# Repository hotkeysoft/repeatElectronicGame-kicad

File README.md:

# Wizard Electronic Game
Rev A October 2019

### Handheld Electronic Game
- ATmega328P microcontroller running at 12MHz
- 4 LEDs
- 4 buttons for play / mode selection
- Buzzer
- Tag-Connect for programming
- Runs on 3 AAA batteries

The microcontroller runs a [TMS1000-series emulator](https://github.com/hotkeysoft/emulators) I made (running in TMS1700 mode).

One ROM is loaded on the emulator: **Pocket Repeat** (by *Tandy/Radio-Shack*).  This is a Simon game clone.

Images
============
|Front                                                 | Back                                              |
|------------------------------------------------------|---------------------------------------------------|
|||

### Schematics (pdf)
- [Complete schematics](./img/schema.pdf)

### PCB Images (svg)
- [Top](./img/pcb-front.svg)
- [Bottom](./img/pcb-back.svg)

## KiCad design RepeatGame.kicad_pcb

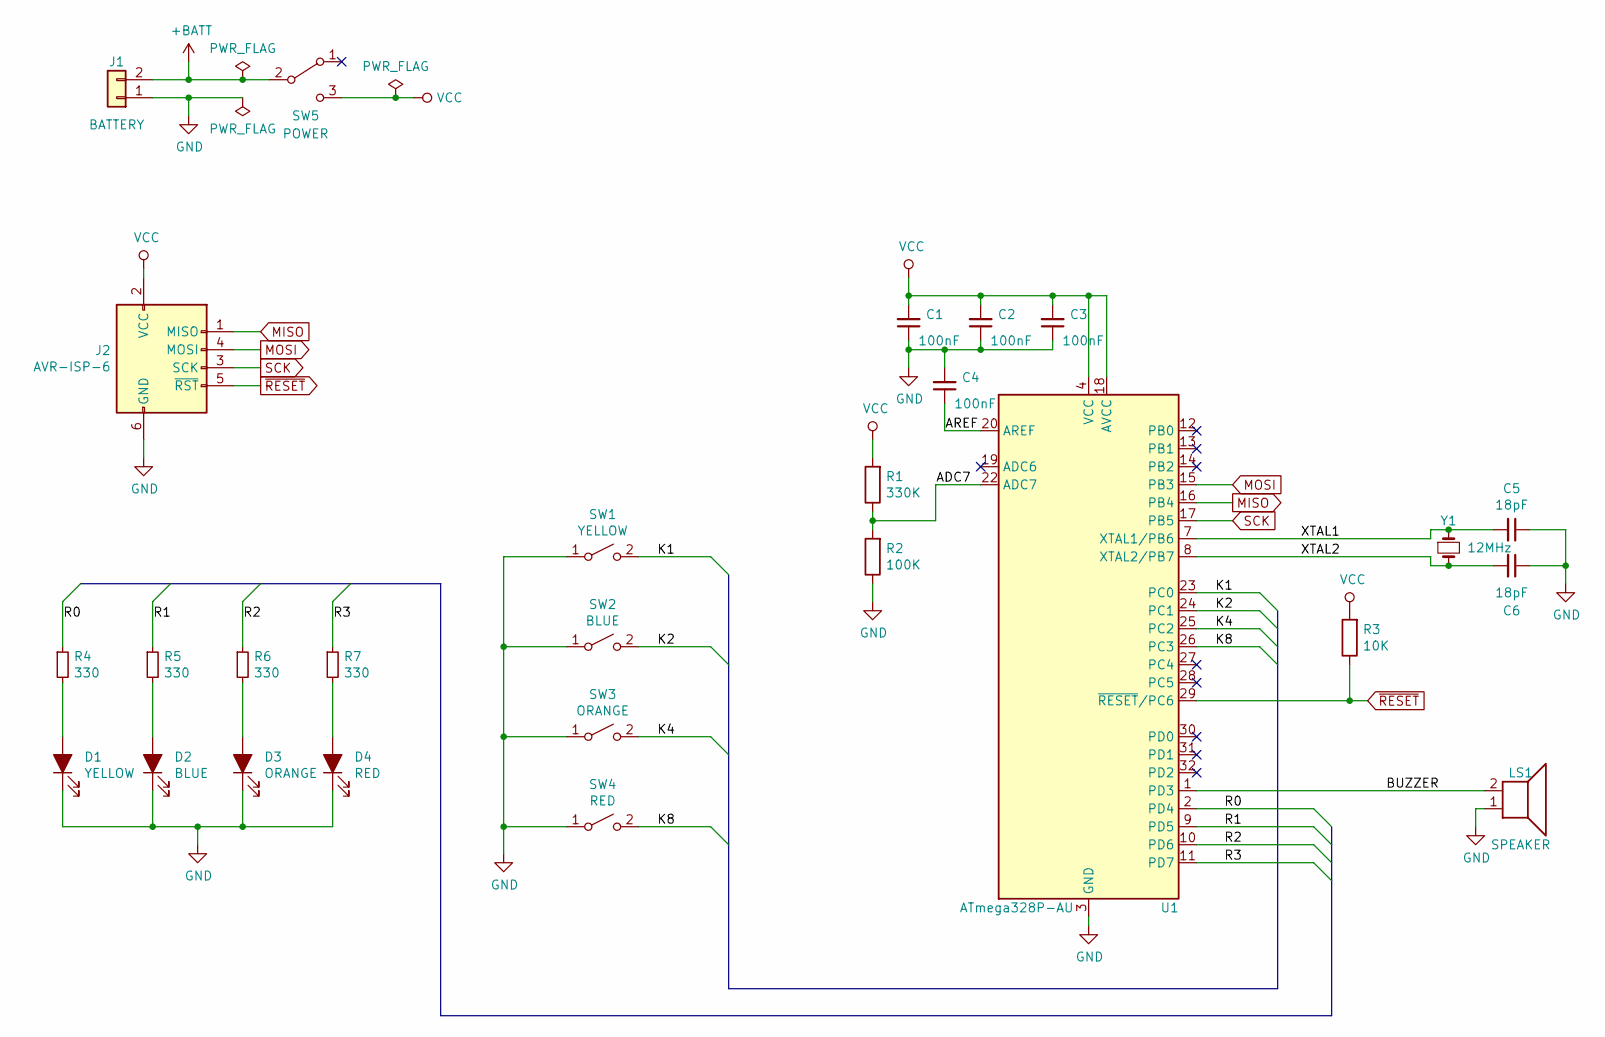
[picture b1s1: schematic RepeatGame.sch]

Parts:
C1, C2, C3, C4: 100nF; C_0805_2012Metric_Pad1.15x1.40mm_HandSolder
C5, C6: 18pF; C_0805_2012Metric_Pad1.15x1.40mm_HandSolder
D1: YELLOW; LED_1206_3216Metric
D2: BLUE; LED_1206_3216Metric
D3: ORANGE; LED_1206_3216Metric
D4: RED; LED_1206_3216Metric
J1: BATTERY; PinHeader_1x02_P2.54mm_Vertical
J2: AVR-ISP-6; Tag-Connect_TC2030-IDC-NL_2x03_P1.27mm_Vertical
LS1: SPEAKER; PinHeader_1x02_P2.54mm_Vertical
R1: 330K; R_0805_2012Metric_Pad1.15x1.40mm_HandSolder
R2: 100K; R_0805_2012Metric_Pad1.15x1.40mm_HandSolder
R3: 10K; R_0805_2012Metric_Pad1.15x1.40mm_HandSolder
R4, R5, R6, R7: 330; R_0805_2012Metric_Pad1.15x1.40mm_HandSolder
SW1: YELLOW; SW_PUSH_6mm
SW2: BLUE; SW_PUSH_6mm
SW3: ORANGE; SW_PUSH_6mm
SW4: RED; SW_PUSH_6mm
SW5: POWER; SW_CuK_OS102011MA1QN1_SPDT_Angled
U1: ATmega328P-AU; TQFP-32_7x7mm_P0.8mm
Y1: 12MHz; Crystal_HC49-4H_Vertical

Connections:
+BATT: J1.2, SW5.2 (B)
/ADC7: R1.1, R2.2, U1.22 (ADC7)
/AREF: C4.1, U1.20 (AREF)
/BUZZER: LS1.2, U1.1 (PD3)
/K1: SW1.2 (B), U1.23 (PC0)
/K2: SW2.2 (B), U1.24 (PC1)
/K4: SW3.2 (B), U1.25 (PC2)
/K8: SW4.2 (B), U1.26 (PC3)
/R0: R4.1, U1.2 (PD4)
/R1: R5.1, U1.9 (PD5)
/R2: R6.1, U1.10 (PD6)
/R3: R7.1, U1.11 (PD7)
/XTAL1: C5.2, U1.7 (XTAL1/PB6), Y1.1
/XTAL2: C6.2, U1.8 (XTAL2/PB7), Y1.2
GND: C1.1, C2.1, C3.1, C4.2, C5.1, C6.1, D1.1 (K), D2.1 (K), D3.1 (K), D4.1 (K), J1.1, J2.6 (GND), LS1.1, R2.1, SW1.1 (A), SW2.1 (A), SW3.1 (A), SW4.1 (A), U1.3 (GND), U1.5 (GND), U1.21 (GND)
MISO: J2.1 (MISO), U1.16 (PB4)
MOSI: J2.4 (MOSI), U1.15 (PB3)
unnamed: D1.2 (A), R4.2
unnamed: D2.2 (A), R5.2
unnamed: D3.2 (A), R6.2
unnamed: D4.2 (A), R7.2
SCK: J2.3 (SCK), U1.17 (PB5)
VCC: C1.2, C2.2, C3.2, J2.2 (VCC), R1.2, R3.2, SW5.3 (C), U1.4 (VCC), U1.6 (VCC), U1.18 (AVCC)
~RESET: J2.5 (~RST), R3.1, U1.29 (~RESET~/PC6)

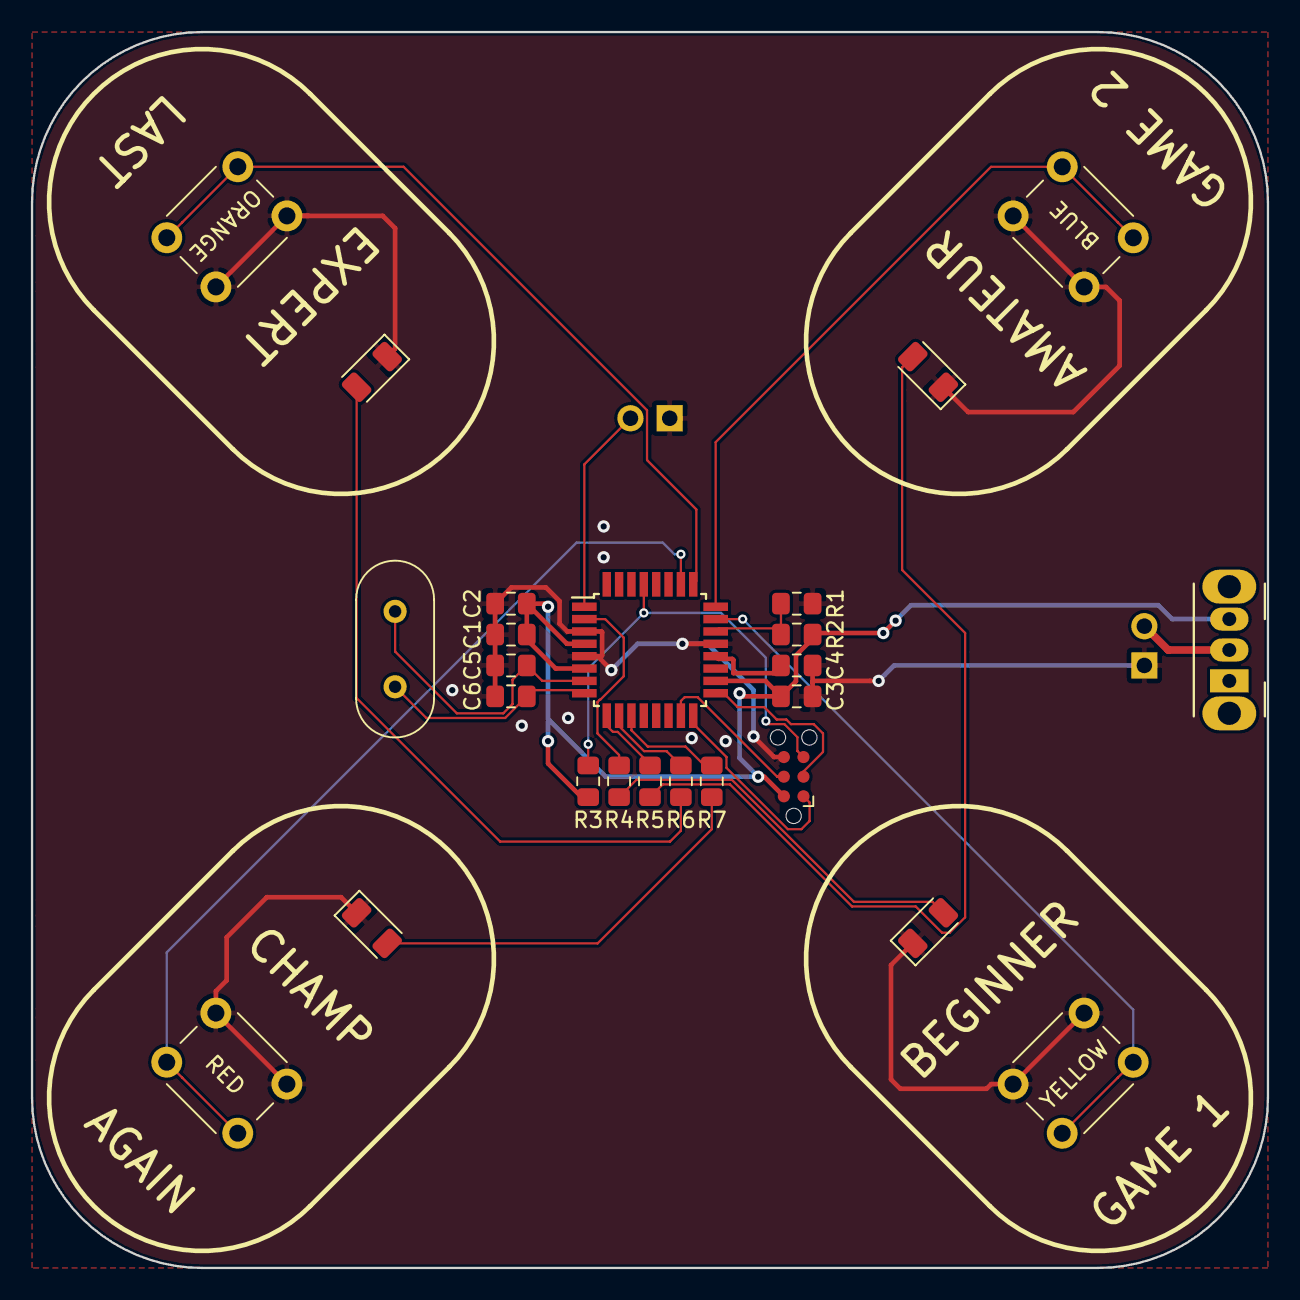
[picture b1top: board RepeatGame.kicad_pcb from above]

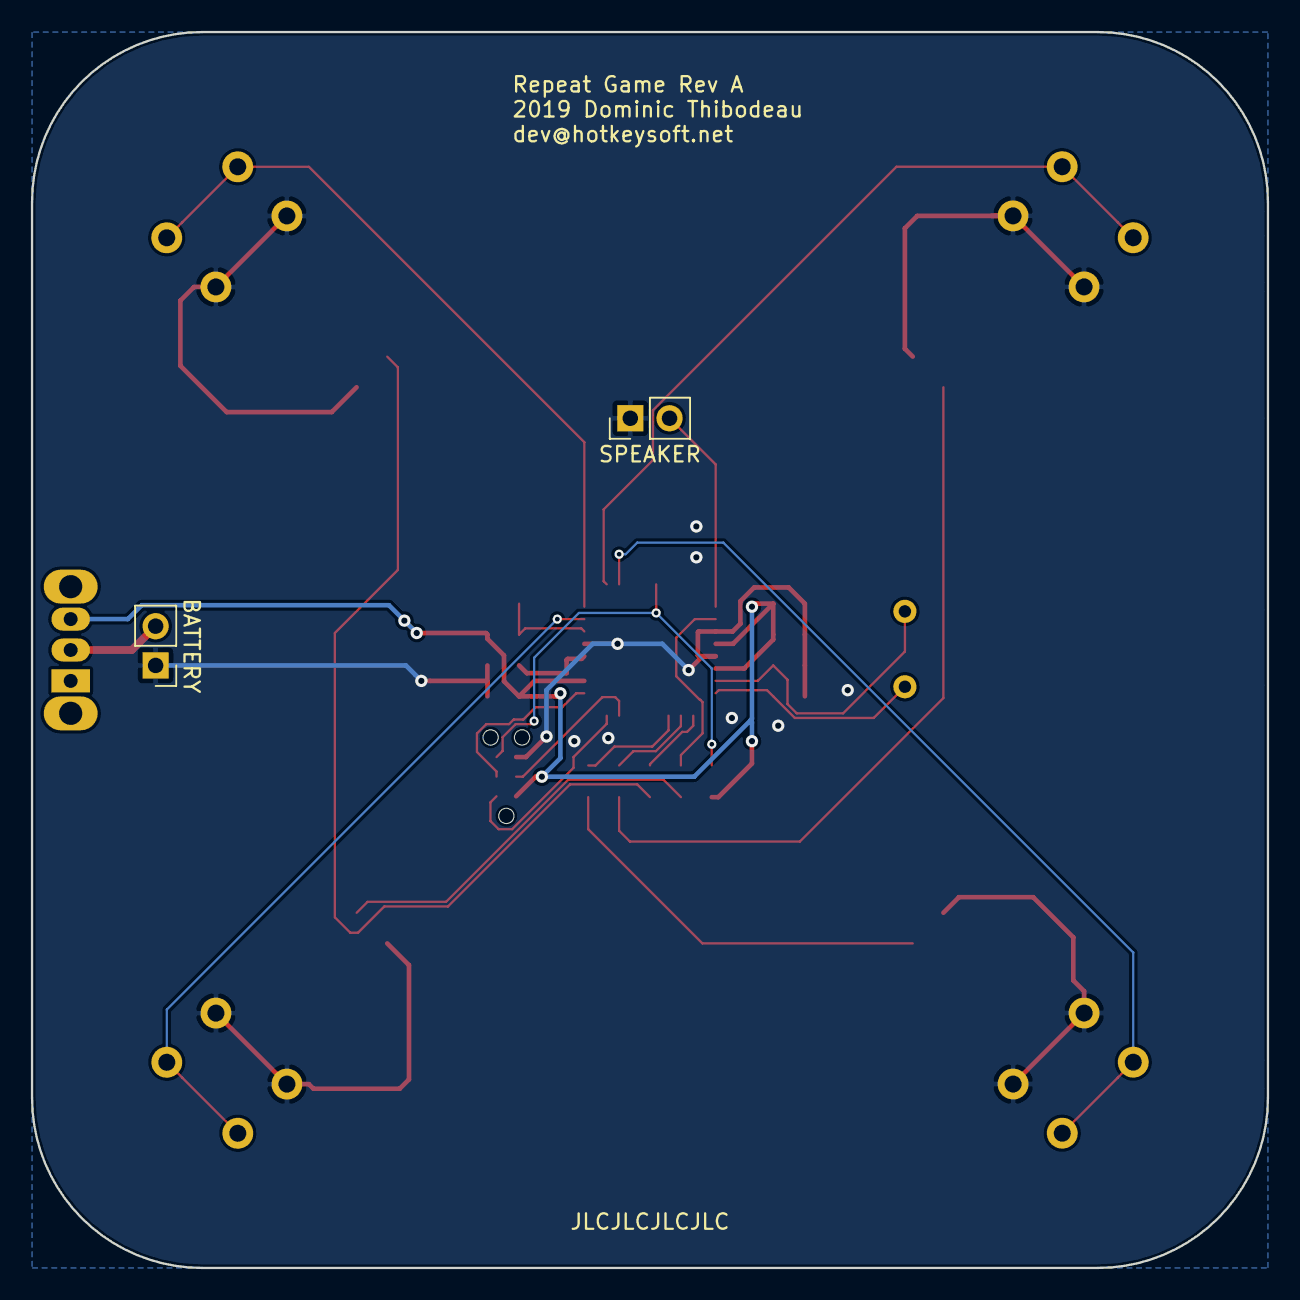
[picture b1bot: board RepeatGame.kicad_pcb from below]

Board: 2 copper layers, 80.0 x 80.0 mm, 27 parts (2 on the bottom side), 24 nets.

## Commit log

2019-10-23 Renamed
2019-10-23 Routing
2019-10-23 Added source
2019-10-24 Added renders
2020-07-28 Cleanup. Added renders
2020-07-28 Create LICENSE
2020-07-28 Updated paths, added submodule commonlib
2020-07-28 png->jpg
2020-07-28 rename
